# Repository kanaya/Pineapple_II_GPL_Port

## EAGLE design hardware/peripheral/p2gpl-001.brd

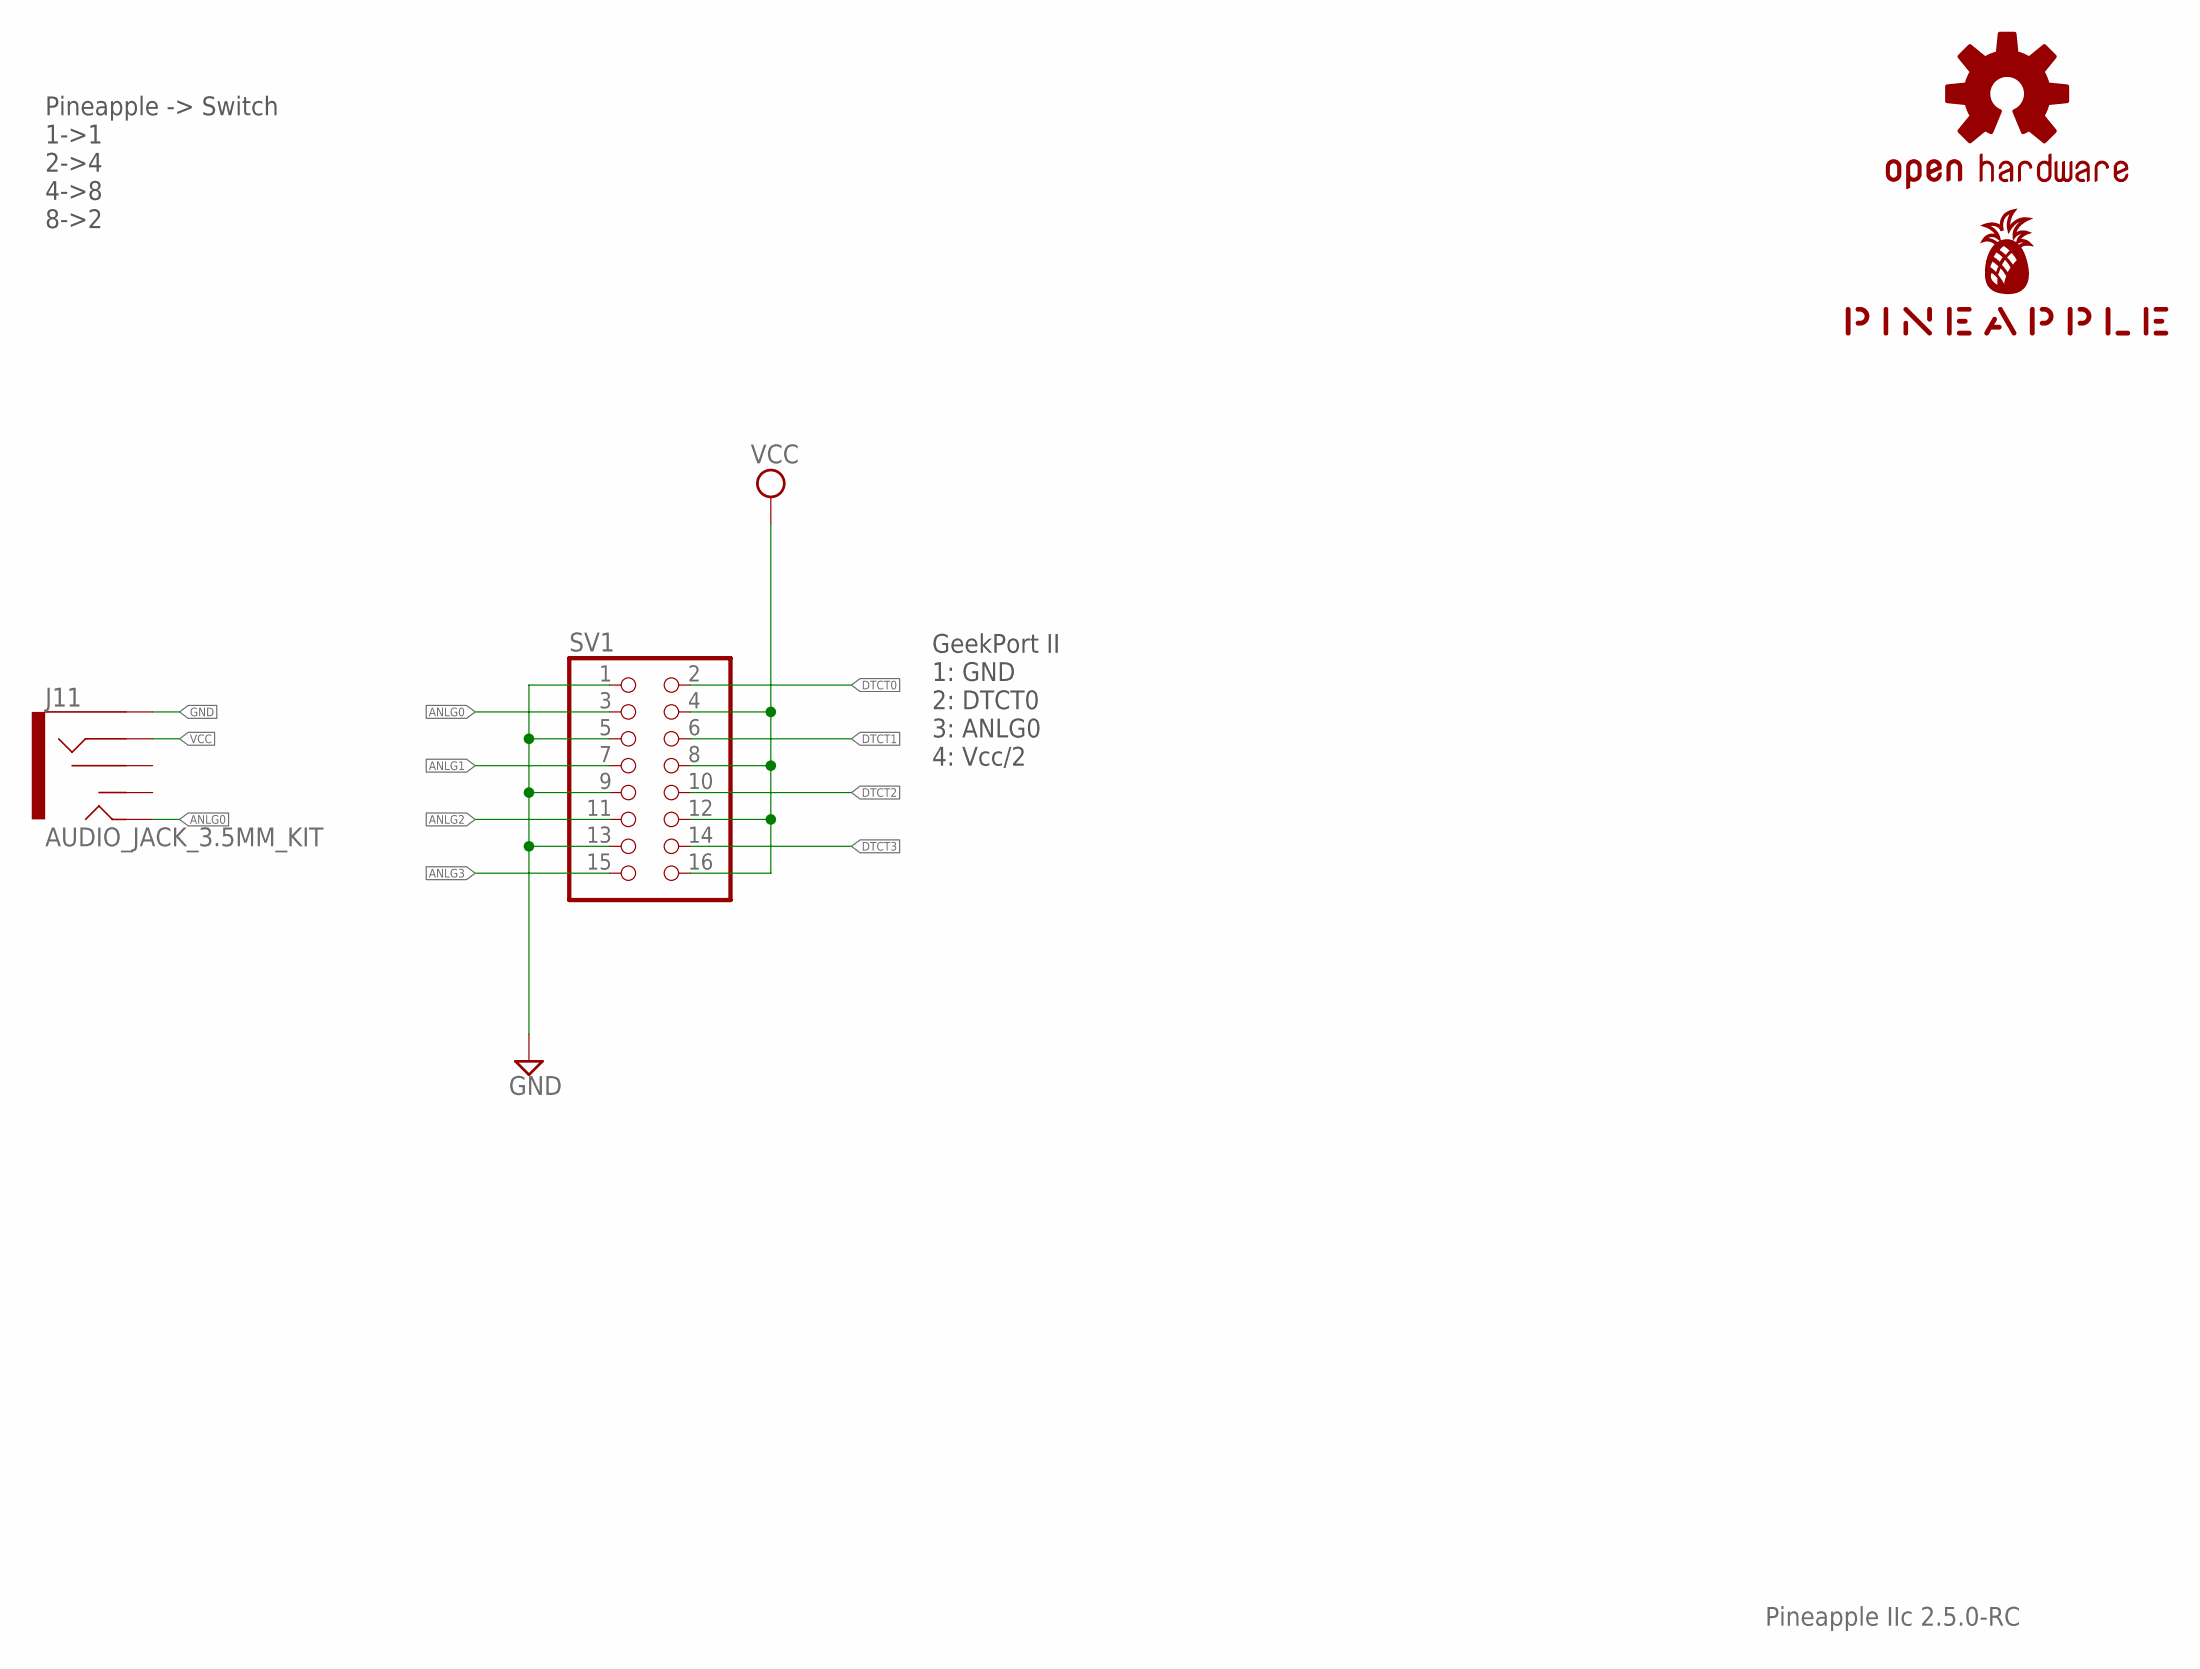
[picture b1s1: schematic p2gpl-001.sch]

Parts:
J11: AUDIO_JACK_3.5MM_KIT; AUDIO-JACK-KIT
LOGO1: OSHW-LOGOS-COPPER; OSHW-LOGO-S_COPPER
SV1: PINHD-2X8; 2X08
U$1: PINEAPPLE450_SILK

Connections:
ANLG0: J11.TIP, SV1.3
ANLG1: SV1.7
ANLG2: SV1.11
ANLG3: SV1.15
DTCT0: SV1.2
DTCT1: SV1.6
DTCT2: SV1.10
DTCT3: SV1.14
GND: J11.SLEEVE, SV1.1, SV1.5, SV1.9, SV1.13
VCC: J11.RING, SV1.4, SV1.8, SV1.12, SV1.16

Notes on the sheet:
Pineapple IIc 2.5.0-RC
Pineapple -> Switch 1->1 2->4 4->8 8->2
GeekPort II 1: GND 2: DTCT0 3: ANLG0 4: Vcc/2

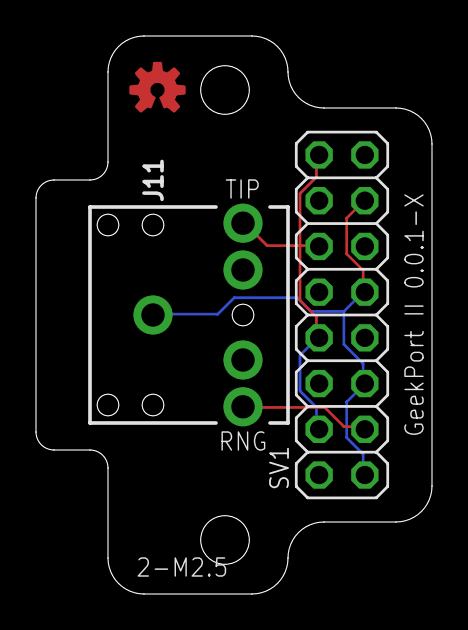
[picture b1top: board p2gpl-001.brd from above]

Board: 2 copper layers, 22.0 x 31.0 mm, 4 parts (1 on the bottom side), 3 nets.

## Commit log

2022-08-24 Imported from 3p Port W.I.P. version.
2022-08-24 Silk.
2022-09-17 GND pattern.
2022-10-14 Fixed polarity of 3.5mm jack.

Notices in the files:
parts and their libraries:
SparkFun-Aesthetics: Licensing: Creative Commons ShareAlike 4.0 International - https://creativecommons.org/licenses/by-sa/4.0
